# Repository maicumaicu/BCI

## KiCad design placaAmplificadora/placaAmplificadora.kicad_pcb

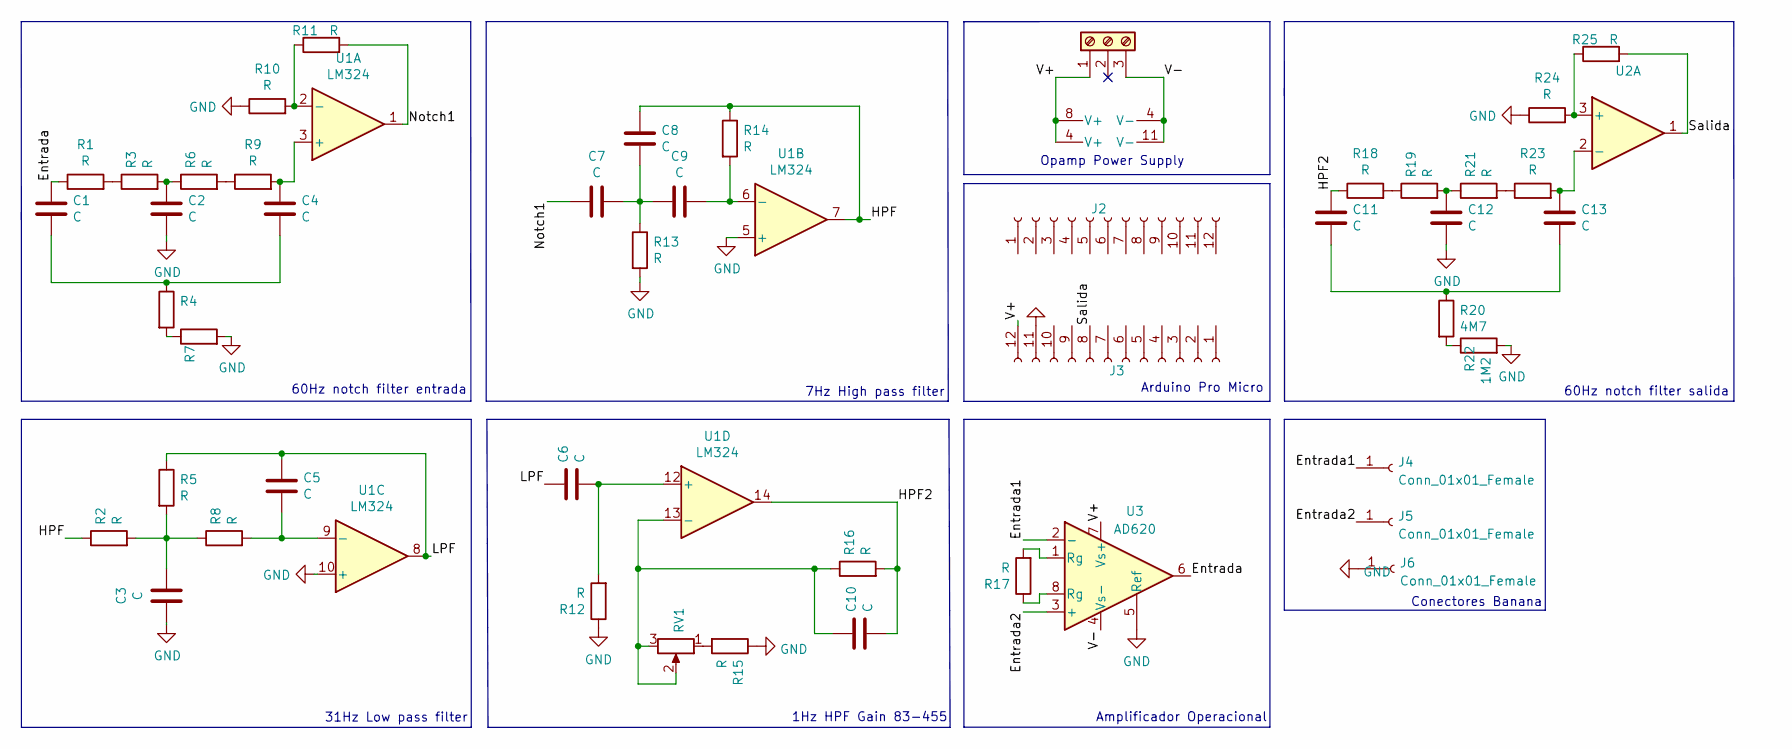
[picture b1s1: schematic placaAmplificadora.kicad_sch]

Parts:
C1, C2, C4, C11, C12, C13: C; C_Disc_D6.0mm_W2.5mm_P5.00mm
C3, C6, C10: C; C_Disc_D6.0mm_W4.4mm_P5.00mm
C5: C; C_Rect_L7.0mm_W4.5mm_P5.00mm
C7, C8, C9: C; C_Rect_L10.3mm_W5.7mm_P7.50mm_MKS4
J1: Screw_Terminal_01x03; TerminalBlock_bornier-3_P5.08mm
J2, J3: Conn_01x12_Female; PinSocket_1x12_P2.54mm_Vertical
J4, J5, J6: Conn_01x01_Female; Banana_Jack_1Pin
R1, R2, R3, R5, R6, R8, R9, R10, R11, R12, R13, R14, R15, R16, R17, R18, R19, R21, R23, R24, R25: R; R_Axial_DIN0207_L6.3mm_D2.5mm_P10.16mm_Horizontal
R4, R7: R_Axial_DIN0207_L6.3mm_D2.5mm_P10.16mm_Horizontal
R20: 4M7; R_Axial_DIN0207_L6.3mm_D2.5mm_P10.16mm_Horizontal
R22: 1M2; R_Axial_DIN0207_L6.3mm_D2.5mm_P10.16mm_Horizontal
RV1: R_Potentiometer; Potentiometer_Bourns_3266W_Vertical
U1: LM324; DIP-14_W7.62mm
U2: LM358; DIP-8_W7.62mm
U3: AD620; DIP-8_W7.62mm

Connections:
/Entrada: C1.1, R1.1, U3.6
/Entrada1: J4.1, U3.2 (-)
/Entrada2: J5.1, U3.3 (+)
/HPF: C8.2, R2.1, R14.1, U1.7
/HPF2: C10.2, C11.1, R16.2, R18.1, U1.14
/LPF: C5.2, C6.1, R5.1, U1.8
/Notch1: C7.1, R11.2, U1.1
/Salida: J3.8, R25.2, U2.1
/V+: J1.1, J3.12, U1.4 (V+), U2.8 (V+), U3.7 (Vs+)
/V-: J1.3, U1.11 (V-), U2.4 (V-), U3.4 (Vs-)
GND: C2.2, C3.1, C12.2, J3.11, J6.1, R7.2, R10.1, R12.1, R13.2, R15.1, R22.2, R24.1, U1.5 (+), U1.10 (+), U3.5 (Ref)
unnamed: C1.2, C4.2, R4.1
unnamed: C2.1, R3.2, R6.1
unnamed: C3.2, R2.2, R5.2, R8.1
unnamed: C4.1, R9.2, U1.3 (+)
unnamed: C5.1, R8.2, U1.9 (-)
unnamed: C6.2, R12.2, U1.12 (+)
unnamed: C7.2, C8.1, C9.1, R13.1
unnamed: C9.2, R14.2, U1.6 (-)
unnamed: C10.1, R16.1, RV1.2, RV1.3, U1.13 (-)
unnamed: C11.2, C13.2, R20.1
unnamed: C12.1, R19.2, R21.1
unnamed: C13.1, R23.2, U2.2 (-)
unnamed: R1.2, R3.1
unnamed: R4.2, R7.1
unnamed: R6.2, R9.1
unnamed: R10.2, R11.1, U1.2 (-)
unnamed: R15.2, RV1.1
unnamed: R17.1, U3.8 (Rg)
unnamed: R17.2, U3.1 (Rg)
unnamed: R18.2, R19.1
unnamed: R20.2, R22.1
unnamed: R21.2, R23.1
unnamed: R24.2, R25.1, U2.3 (+)

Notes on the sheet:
Conectores Banana
7Hz High pass filter
Opamp Power Supply
Arduino Pro Micro
31Hz Low pass filter
60Hz notch filter entrada
60Hz notch filter salida
1Hz HPF Gain 83-455
Amplificador Operacional

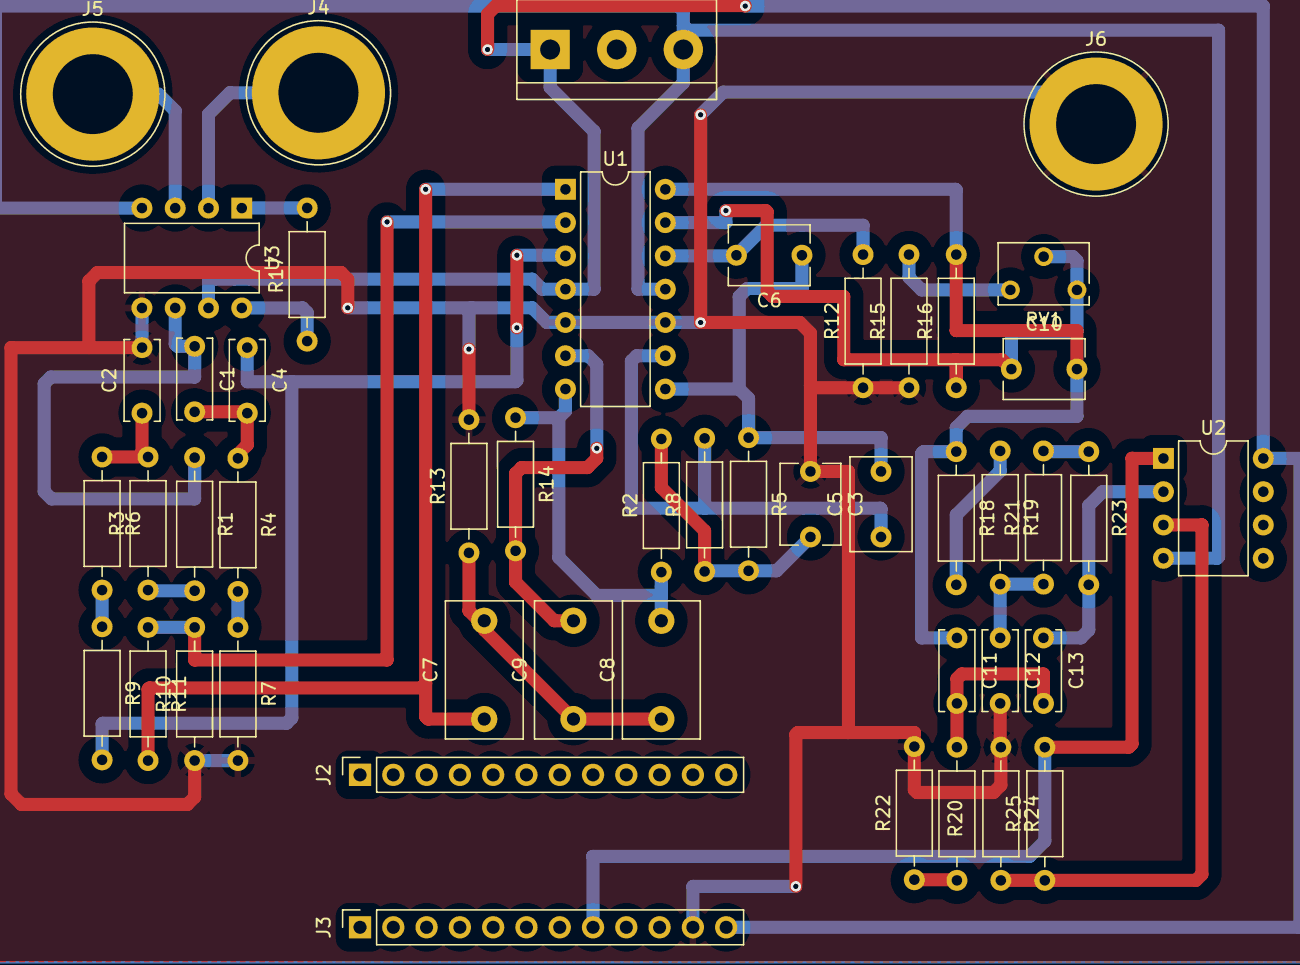
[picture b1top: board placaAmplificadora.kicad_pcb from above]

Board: 2 copper layers, 48 parts (0 on the bottom side), 34 nets.
